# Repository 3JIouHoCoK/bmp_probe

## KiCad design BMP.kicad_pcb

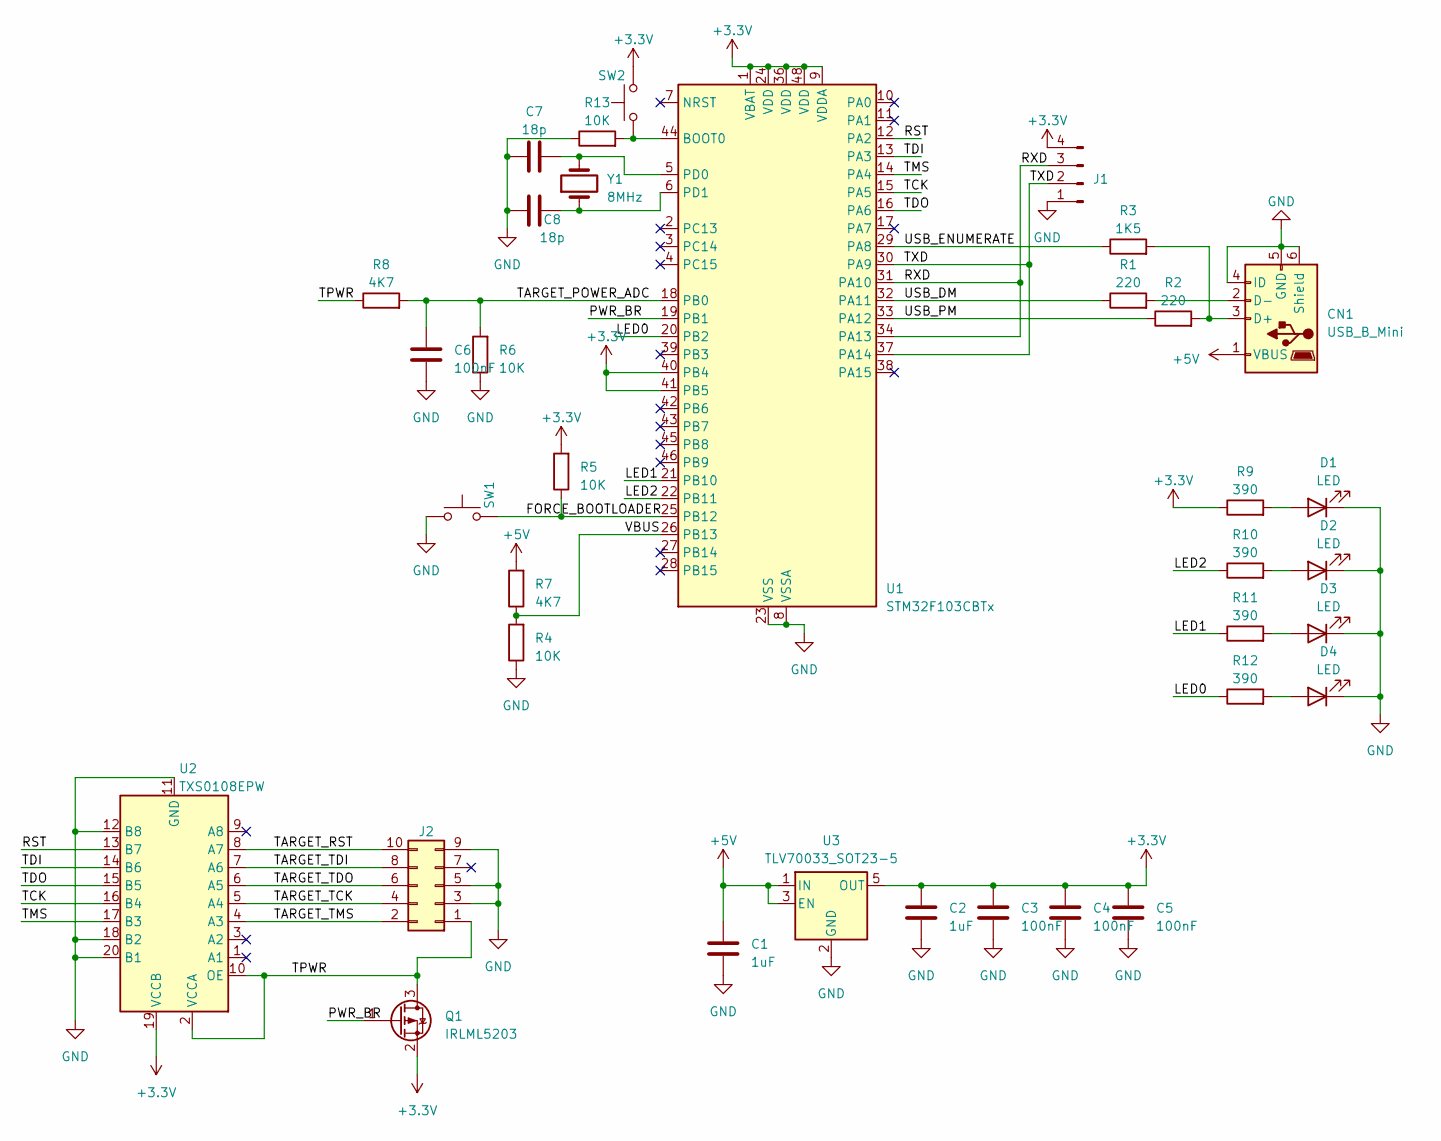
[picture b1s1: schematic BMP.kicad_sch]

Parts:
C1, C2: 1uF; C_0805_2012Metric_Pad1.18x1.45mm_HandSolder
C3, C4, C5, C6: 100nF; C_0603_1608Metric_Pad1.08x0.95mm_HandSolder
C7, C8: 18p; C_0603_1608Metric_Pad1.08x0.95mm_HandSolder
CN1: USB_B_Mini; USB_Mini-B_Lumberg_2486_01_Horizontal
D1, D2, D3, D4: LED; R_0603_1608Metric_Pad0.98x0.95mm_HandSolder
J1: Conn_01x04_Pin; PinHeader_1x04_P2.54mm_Vertical
J2: Conn_02x05_Odd_Even; IDC-Header_2x05_P2.54mm_Vertical
Q1: IRLML5203; SOT-23
R1, R2: 220; R_0603_1608Metric_Pad0.98x0.95mm_HandSolder
R3: 1K5; R_0603_1608Metric_Pad0.98x0.95mm_HandSolder
R4, R5, R6, R13: 10K; R_0603_1608Metric_Pad0.98x0.95mm_HandSolder
R7, R8: 4K7; R_0603_1608Metric_Pad0.98x0.95mm_HandSolder
R9, R10, R11, R12: 390; R_0603_1608Metric_Pad0.98x0.95mm_HandSolder
SW1, SW2: SW_Push; BMP_SWITCH_2PIN
U1: STM32F103CBTx; LQFP-48_7x7mm_P0.5mm
U2: TXS0108EPW; TSSOP-20_4.4x6.5mm_P0.65mm
U3: TLV70033_SOT23-5; SOT-23-5
Y1: 8MHz; Crystal_HC18-U_Vertical

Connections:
+3.3V: C2.2, C3.2, C4.2, C5.2, J1.4, Q1.2 (S), R5.2, R9.1, SW2.2, U1.1 (VBAT), U1.9 (VDDA), U1.24 (VDD), U1.36 (VDD), U1.40 (PB4), U1.41 (PB5), U1.48 (VDD), U2.19 (VCCB), U3.5 (OUT)
+5V: C1.2, CN1.1 (VBUS), R7.2, U3.1 (IN), U3.3 (EN)
/FORCE_BOOTLOADER: R5.1, SW1.2, U1.25 (PB12)
/LED0: R12.1, U1.20 (PB2)
/LED1: R11.1, U1.21 (PB10)
/LED2: R10.1, U1.22 (PB11)
/PWR_BR: Q1.1 (G), U1.19 (PB1)
/RST: U1.12 (PA2), U2.13 (B7)
/RXD: J1.3, U1.31 (PA10), U1.34 (PA13)
/TARGET_POWER_ADC: C6.2, R6.2, R8.2, U1.18 (PB0)
/TARGET_RST: J2.10, U2.8 (A7)
/TARGET_TCK: J2.4, U2.5 (A4)
/TARGET_TDI: J2.8, U2.7 (A6)
/TARGET_TDO: J2.6, U2.6 (A5)
/TARGET_TMS: J2.2, U2.4 (A3)
/TCK: U1.15 (PA5), U2.16 (B4)
/TDI: U1.13 (PA3), U2.14 (B6)
/TDO: U1.16 (PA6), U2.15 (B5)
/TMS: U1.14 (PA4), U2.17 (B3)
/TPWR: J2.1, Q1.3 (D), R8.1, U2.2 (VCCA), U2.10 (OE)
/TXD: J1.2, U1.30 (PA9), U1.37 (PA14)
/USB_DM: R1.1, U1.32 (PA11)
/USB_ENUMERATE: R3.1, U1.29 (PA8)
/USB_PM: R2.1, U1.33 (PA12)
/VBUS: R4.2, R7.1, U1.26 (PB13)
GND: C1.1, C2.1, C3.1, C4.1, C5.1, C6.1, C7.1, C8.1, CN1.4 (ID), CN1.5 (GND), CN1.6 (Shield), D1.1 (K), D2.1 (K), D3.1 (K), D4.1 (K), J1.1, J2.3, J2.5, J2.9, R4.1, R6.1, R13.1, SW1.1, U1.8 (VSSA), U1.23 (VSS), U1.35 (VSS), U1.47 (VSS), U2.11 (GND), U2.12 (B8), U2.18 (B2), U2.20 (B1), U3.2 (GND)
unnamed: CN1.3 (D+), R2.2, R3.2
unnamed: CN1.2 (D-), R1.2
unnamed: D1.2 (A), R9.2
unnamed: D2.2 (A), R10.2
unnamed: D3.2 (A), R11.2
unnamed: D4.2 (A), R12.2
unnamed: R13.2, SW2.1, U1.44 (BOOT0)
unnamed: C7.2, U1.5 (PD0), Y1.2
unnamed: C8.2, U1.6 (PD1), Y1.1

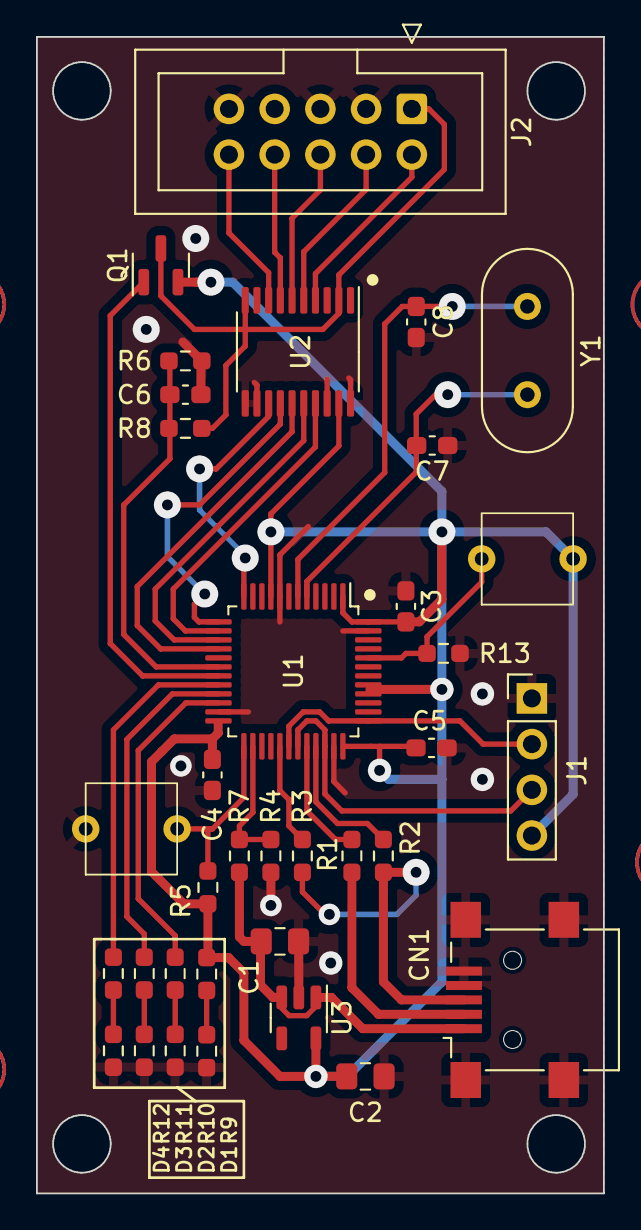
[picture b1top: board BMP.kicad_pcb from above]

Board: 2 copper layers, 31.5 x 64.2 mm, 35 parts (0 on the bottom side), 35 nets.

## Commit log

2023-03-14 14032023
2023-03-14 schematic done
2023-03-15 15032023
2023-03-16 beta PCB complete
2023-03-17 17032023
2023-03-18 18032022
2023-04-29 29042023
